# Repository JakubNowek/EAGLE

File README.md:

<br />
<div align="center">
  <h2 align="center">Electronics in Automation</h3>

  <p align="center">
    7-Segment Display Clock Project
    <br />
    <br />
    <a href="https://github.com/JakubNowek/EAGLE/issues">Report Bug</a>
    ·
    <a href="https://github.com/JakubNowek/EAGLE/issues">Request Feature</a>
  </p>
</div>

<!-- TABLE OF CONTENTS -->
<details>
  <summary>Table of Contents</summary>
  <ol>
    <li>
      <a href="#about-the-project">About The Project</a>
    </li>
    <li><a href="#finished-project">Finished Project</a>
    </li>
    <li><a href="#pcb-layout">PCB layout</a></li>
    <li><a href="#arduino-code">Arduino Code</a></li>
    <li><a href="#bill-of-materials">Bill of materials</a></li>
  </ol>
</details>

## About the Project
The ESP-01s module connects to NTP server and retrives information about the current date from it. Next data is forwarded towards Arduino Pro-Mini which extracts the time in hours, minutes and seconds and sends them towards 7-segments display through shift register.
Everything is powered up by a 7.5-25V power supply, the power of which is reduced to 5V by a voltage stabilizer.

## Finished Project

## PCB layout
Layout was auto generated using Altium Designer.

## Arduino Code
Used code for ESP module and Pro-Mini board can be found [here](projects/Serial_NTP_clock/ESP8266_with_NTP_code.ino) and [here](projects/Serial_NTP_clock/Pro_mini_code.ino).

## Bill of materials
| Qty | Value       | Device              |
|-----|-------------|---------------------|
| 2   |             | 7SEG-CA             |
| 6   |             | BC556A-PNP-TO92-EBC |
| 2   | 0.1u        | C-EU025-025X050     |
| 6   | 100         | R-EU_0414/15        |
| 1   | 10u         | C-EU025-025X050     |
| 10  | 220         | R-EU_0414/15        |
| 1   | 2k2         | R-EU_0414/15        |
| 2   | 470u/25V    | CPOL-EUE5-8.5       |
| 1   | 74HC595N    | 74HC595N            |
| 1   | 7805T       | 7805T               |
| 1   | DCJ0202     | DCJ0202             |
| 1   | ESP-01      | ESP-01              |
| 1   | LD117AV     | LD117AV             |
| 1   | LDQ-M3604RI | LDQ-M3604RI         |
| 1   | PRO-MINI    | PRO-MINI            |

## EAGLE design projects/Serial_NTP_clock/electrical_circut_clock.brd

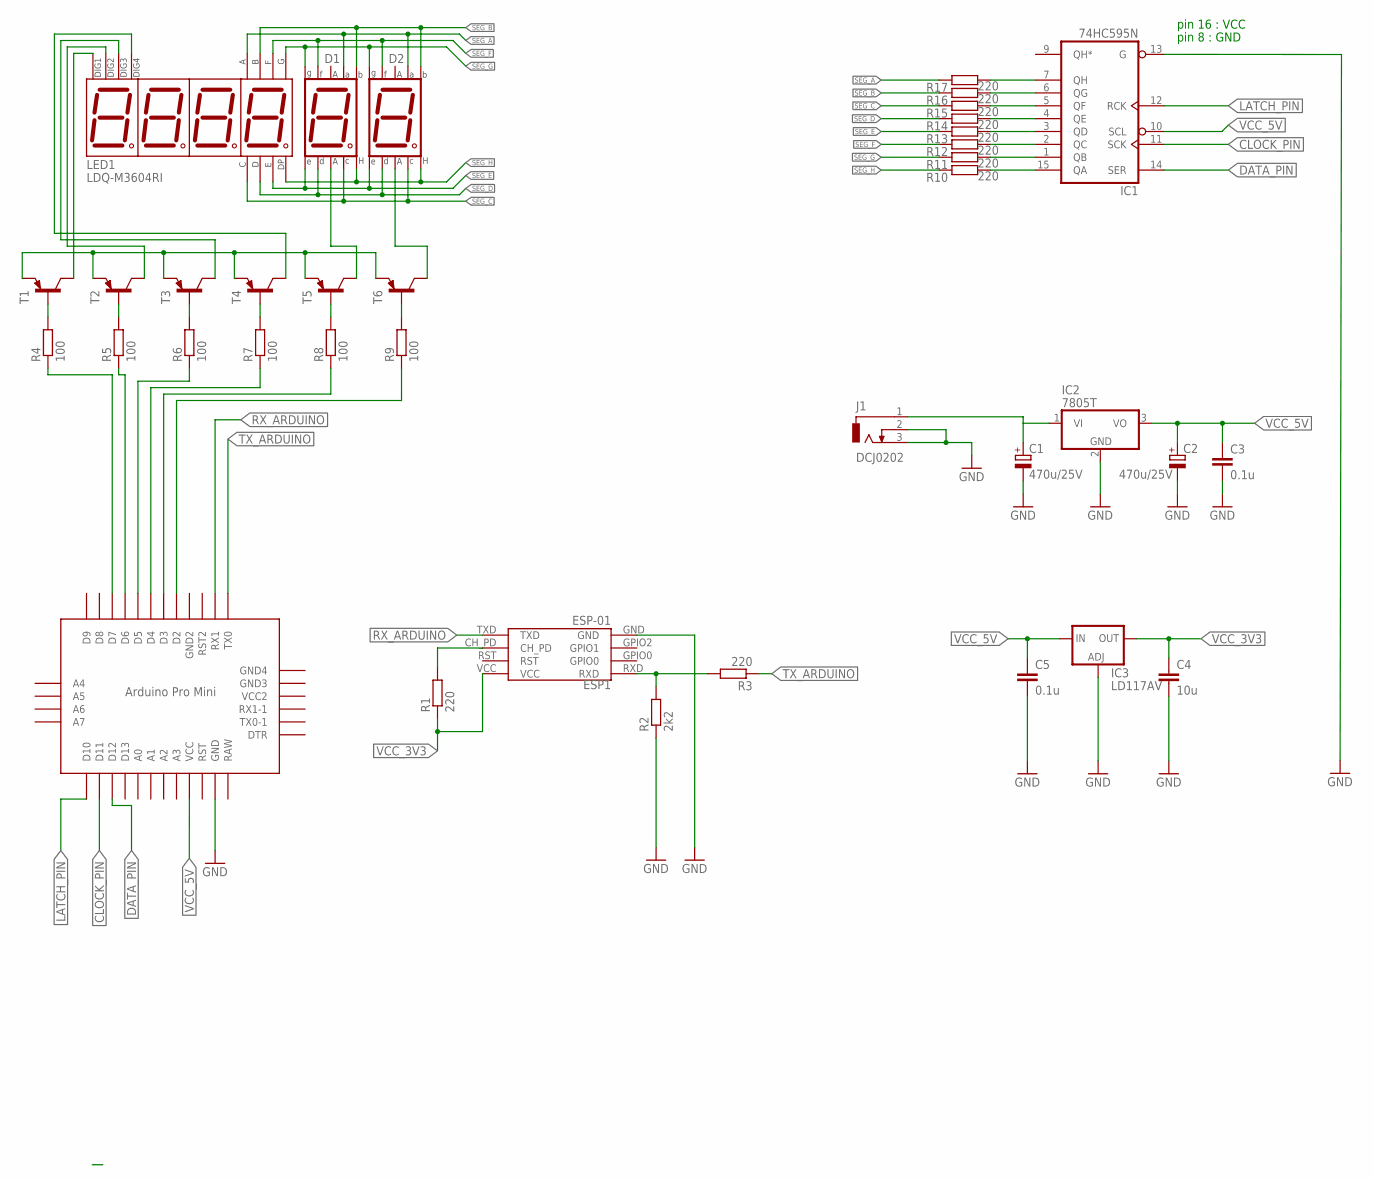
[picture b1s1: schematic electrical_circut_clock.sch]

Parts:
C1, C2: 470u/25V; E5-8,5
C3, C5: 0.1u; C025-025X050
C4: 10u; C025-025X050
D1, D2: 7SEG-CA; 7SEG-13
ESP1: ESP-01
IC1: 74HC595N; DIL16
IC2: 7805T; TO220H
IC3: LD117AV; TO220L1
J1: DCJ0202
LED1: LDQ-M3604RI
R1, R3, R10, R11, R12, R13, R14, R15, R16, R17: 220; 0204/7
R2: 2k2; 0204/7
R4, R5, R6, R7, R8, R9: 100; 0204/7
T1, T2, T3, T4, T5, T6: BC556A-PNP-TO92-EBC; TO92-EBC
U$1: PRO-MINI

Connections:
CLOCK_PIN: IC1.11 (SCK), U$1.D11
DATA_PIN: IC1.14 (SER), U$1.D12
GND: C1.-, C2.-, C3.2, C4.2, C5.2, ESP1.GND, IC1.8 (GND), IC1.13 (G), IC2.2 (GND), IC3.1 (ADJ), J1.2, J1.3, R2.1, U$1.GND
LATCH_PIN: IC1.12 (RCK), U$1.D10
unnamed: R4.2, T1.B
unnamed: R5.2, T2.B
unnamed: R6.2, T3.B
unnamed: R7.2, T4.B
unnamed: R8.2, T5.B
unnamed: R9.2, T6.B
unnamed: T1.E, T2.E, T3.E, T4.E, T5.E, T6.E
unnamed: LED1.9 (DIG2), T2.C
unnamed: R4.1, U$1.D7
unnamed: ESP1.CH_PD, R1.2
unnamed: IC1.15 (QA), R10.2
unnamed: IC1.1 (QB), R11.2
unnamed: IC1.2 (QC), R12.2
unnamed: IC1.3 (QD), R13.2
unnamed: IC1.4 (QE), R14.2
unnamed: IC1.5 (QF), R15.2
unnamed: IC1.6 (QG), R16.2
unnamed: IC1.7 (QH), R17.2
unnamed: LED1.12 (DIG1), T1.C
unnamed: LED1.8 (DIG3), T3.C
unnamed: LED1.6 (DIG4), T4.C
unnamed: D1.8 (CA2), T5.C
unnamed: D2.8 (CA2), T6.C
unnamed: R5.1, U$1.D6
unnamed: R6.1, U$1.D5
unnamed: R7.1, U$1.D4
unnamed: R8.1, U$1.D3
unnamed: R9.1, U$1.D2
RAW: U$1.RAW
RX_ARDUINO: ESP1.TXD, U$1.RX1
SEG_A: D1.7 (A), D2.7 (A), LED1.11 (A), R17.1
SEG_B: D1.6 (B), D2.6 (B), LED1.7 (B), R16.1
SEG_C: D1.4 (C), D2.4 (C), LED1.4 (C), R15.1
SEG_D: D1.2 (D), D2.2 (D), LED1.2 (D), R14.1
SEG_E: D1.1 (E), D2.1 (E), LED1.1 (E), R13.1
SEG_F: D1.9 (F), D2.9 (F), LED1.10 (F), R12.1
SEG_G: D1.10 (G), D2.10 (G), LED1.5 (G), R11.1
SEG_H: D1.5 (DP), D2.5 (DP), LED1.3 (DP), R10.1
TX_ARDUINO: ESP1.RXD, R2.2, R3.1, R3.2, U$1.TX0
VCC: IC1.16 (VCC)
VCC_3V3: C4.1, ESP1.VCC, IC3.2 (OUT), R1.1
VCC_5V: C2.+, C3.1, C5.1, IC1.10 (SCL), IC2.3 (VO), IC3.3 (IN), U$1.VCC
VIN_9V: C1.+, IC2.1 (VI), J1.1

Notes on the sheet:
pin 16 : VCC
pin 8 : GND

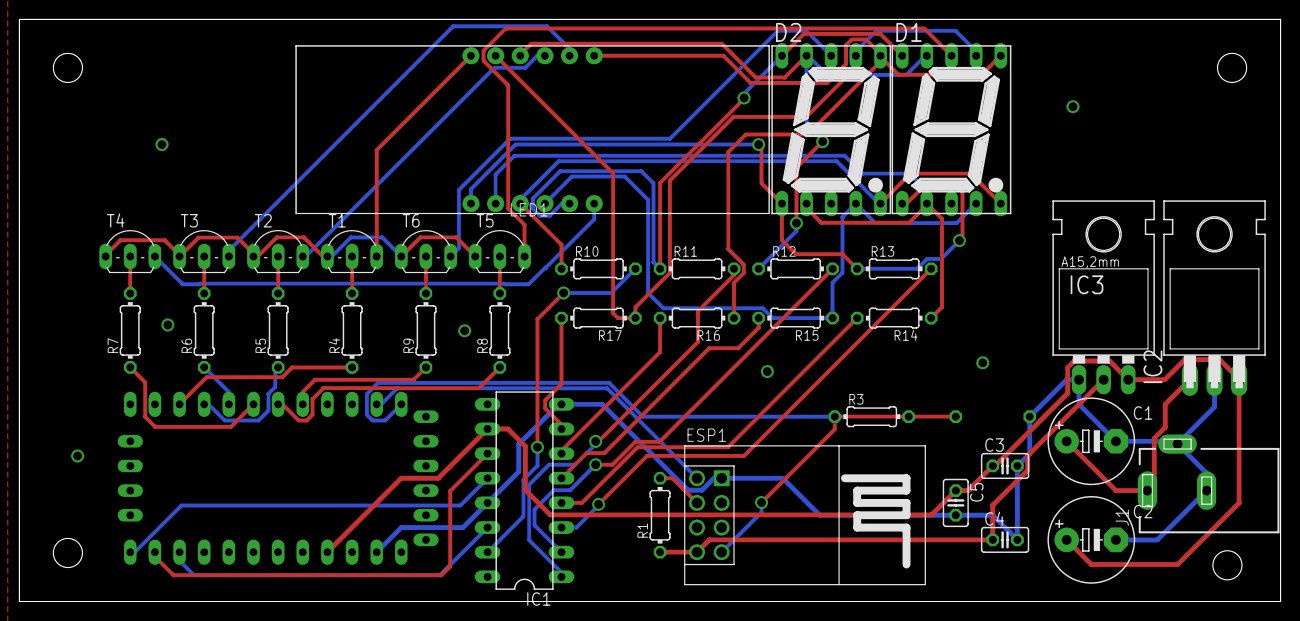
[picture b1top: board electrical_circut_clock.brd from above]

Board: 2 copper layers, 130.0 x 60.0 mm, 37 parts (1 on the bottom side), 45 nets.

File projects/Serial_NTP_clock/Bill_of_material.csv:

"Qty";"Value";"Device";"Package";"Parts";"Description";"AVAILABILITY";"DESCRIPTION";"MF";"MP";"MPN";"OC_FARNELL";"OC_NEWARK";"PACKAGE";"POPULARITY";"PRICE";"SPICEPREFIX";
"2";"";"7SEG-CA";"7SEG-13";"D1, D2";"7-segment DISPLAY";"";"";"";"";"";"";"";"";"5";"";"";
"6";"";"BC556A-PNP-TO92-EBC";"TO92-EBC";"T1, T2, T3, T4, T5, T6";"PNP Transistror";"";"";"";"";"";"";"";"";"0";"";"";
"2";"0.1u";"C-EU025-025X050";"C025-025X050";"C3, C5";"CAPACITOR, European symbol";"";"";"";"";"";"";"";"";"65";"";"C";
"6";"100";"R-EU_0414/15";"0414/15";"R4, R5, R6, R7, R8, R9";"RESISTOR, European symbol";"";"";"";"";"";"";"";"";"0";"";"R";
"1";"10u";"C-EU025-025X050";"C025-025X050";"C4";"CAPACITOR, European symbol";"";"";"";"";"";"";"";"";"65";"";"C";
"10";"220";"R-EU_0414/15";"0414/15";"R1, R3, R10, R11, R12, R13, R14, R15, R16, R17";"RESISTOR, European symbol";"";"";"";"";"";"";"";"";"0";"";"R";
"1";"2k2";"R-EU_0414/15";"0414/15";"R2";"RESISTOR, European symbol";"";"";"";"";"";"";"";"";"0";"";"R";
"2";"470u/25V";"CPOL-EUE5-8.5";"E5-8,5";"C1, C2";"POLARIZED CAPACITOR, European symbol";"";"";"";"";"";"";"";"";"0";"";"C";
"1";"74HC595N";"74HC595N";"DIL16";"IC1";"8-bit SHIFT REGISTER, output latch";"";"";"";"";"";"";"";"";"0";"";"";
"1";"7805T";"7805T";"TO220H";"IC2";"Positive VOLTAGE REGULATOR";"";"";"";"";"";"";"";"";"";"";"";
"1";"DCJ0202";"DCJ0202";"DCJ0202";"J1";"DC POWER JACK";"";"";"";"";"";"unknown";"unknown";"";"17";"";"";
"1";"ESP-01";"ESP-01";"ESP-01";"ESP1";"Check prices";"Not in stock";" ESP-01M ESP8266 DIP Adapter series Transceiver";" 802.11 b/g/n (Wi-Fi, WiFi, WLAN) Evaluation Board ";"AI-Thinker";"ESP-01";"";"";"";"Non-Standard AI-Thinker";"";"None";
"1";"LD117AV";"LD117AV";"TO220L1";"IC3";"Low drop fixed and adjustable positive voltage regulators 1 A";"";"";"";"";"";"";"";"";"0";"";"";
"1";"LDQ-M3604RI";"LDQ-M3604RI";"LDQ-M3604RI";"LED1";"Check prices";"In Stock";" Display, Seven Segment, 9.2MM, Red ";"Lumex";"LDQ-M3604RI";"";"";"";"None";"";"None";"";
"1";"PRO-MINI";"PRO-MINI";"PRO-MINI";"U$1";"Arduion Pro Mini Clone V1.0";"";"";"";"";"";"";"";"";"";"";"";

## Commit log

2022-01-03 new arduino uno symbol
2022-01-03 added labels
2022-01-03 labels of 7-seg rearanged
2022-01-03 completed lm7805 schematics
2022-01-04 added 3v3voltage regulator and rearanged
2022-01-04 final rearangement?
    nie wiem czy nie zmienić tego arduino na coś normalnego i co z tymi pinami zasilania rejestru przesuwnego?
2022-01-05 changed arduino to pro mini
2022-01-12 repaired gnd connection
2022-01-12 repair v2
2022-01-13 Added board with mounting holes and started designing power module
2022-01-13 Done power section
2022-01-13 Added ESP-01 module
2022-01-13 Connected display module
2022-01-14 Completed first revision of pcb design
2022-01-14 Fixed overlapping circuit
2022-01-15 Added power jack
2022-01-15 moved resistors for better thermal flow
2022-01-26 changed resistors type
2022-01-26 Second revision of pcb layout
2022-01-30 Added code for arduino and esp
2022-01-30 renamed arduino code
2022-01-30 renamed esp code
2022-01-30 renamed pcb file
2022-01-30 created clock folder
2022-01-30 Grounded plate, relocated module of scheme and added more vias
2022-01-31 fixed consistency problems
2022-01-31 Generated gerbare files
2022-02-19 Added counter circuit
2022-02-19 circuit pdf update
